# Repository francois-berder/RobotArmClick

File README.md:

## RobotArmClick

The robot arm click is a small board which uses the Mikrobus interface to control 4 servos using I2C.

This repository contains:
  - The pcb design
  - The firwmare of the PIC present on the RobotArmClick
  - Some tests to verify the firmware

For more information about the firmware and the tests, have a look at these repositories:
  - https://github.com/francois-berder/RobotArmClick-tests
  - https://github.com/francois-berder/RobotArmClick-firmware

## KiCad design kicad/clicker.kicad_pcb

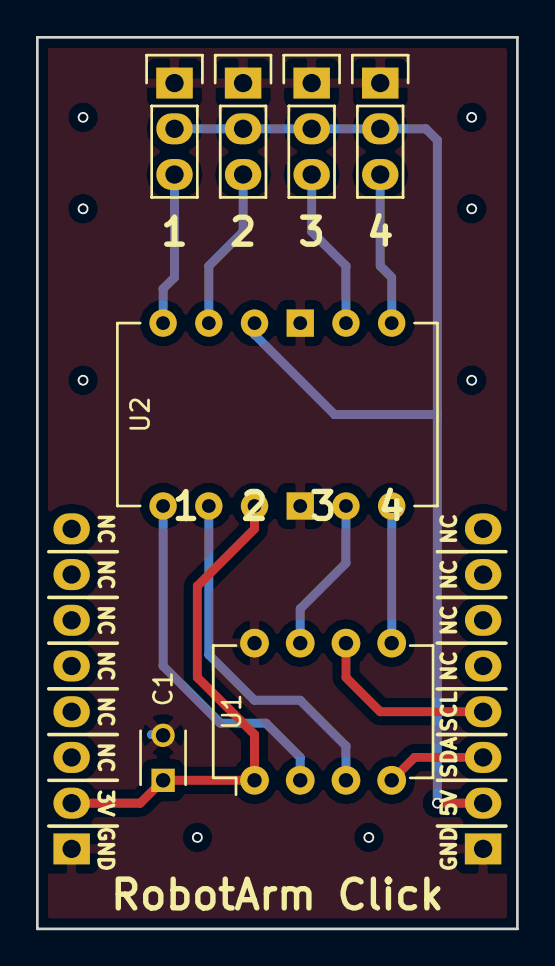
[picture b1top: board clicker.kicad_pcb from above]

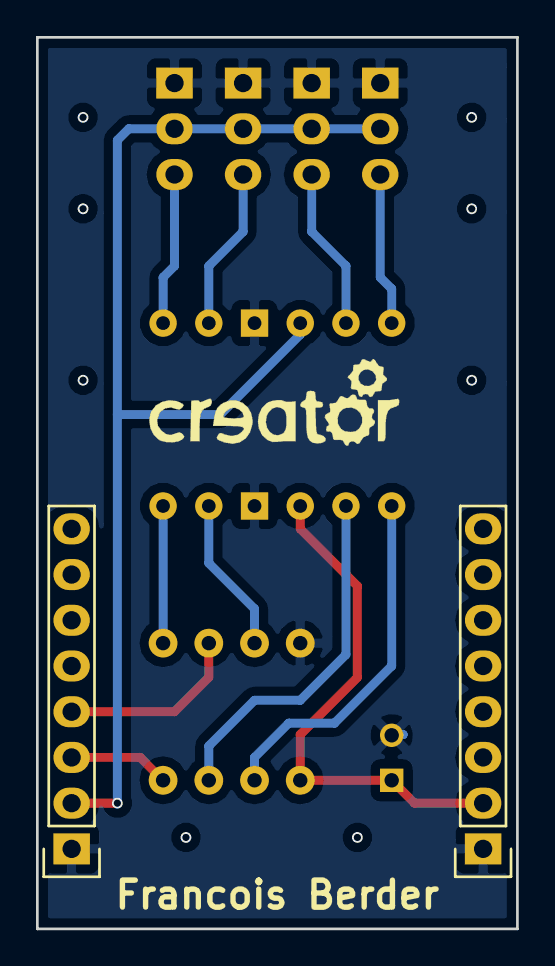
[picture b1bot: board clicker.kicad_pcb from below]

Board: 2 copper layers, 26.7 x 49.5 mm, 9 parts (2 on the bottom side), 13 nets.

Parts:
C1: C; C_Disc_D3_P2.5
U1: PIC12(L)F1552; DIP-8_W7.62mm
U2: LOGIC_LEVEL_CONVERTER
U3: MIKROBUS_CON_L; Pin_Header_Straight_1x08
U4: MIKROBUS_CON_R; Pin_Header_Straight_1x08
U5, U6, U7, U8: SERVO_CON; Pin_Header_Straight_1x03

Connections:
+3V3: C1.1, U1.1, U2.9, U3.2
+5V: U2.3, U4.2, U5.2, U6.2, U7.2, U8.2
/MIKROBUS_SCL: U1.6, U4.4
/MIKROBUS_SDA: U1.4, U4.3
/SERVO_CON_0_SIG: U1.5, U2.12
/SERVO_CON_0_SIG_5V: U2.6, U5.3
/SERVO_CON_1_SIG: U1.7, U2.11
/SERVO_CON_1_SIG_5V: U2.5, U6.3
/SERVO_CON_2_SIG: U1.3, U2.8
/SERVO_CON_2_SIG_5V: U2.2, U7.3
/SERVO_CON_3_SIG: U1.2, U2.7
/SERVO_CON_3_SIG_5V: U2.1, U8.3
GND: C1.2, U1.8, U2.4, U2.10, U3.1, U4.1, U5.1, U6.1, U7.1, U8.1

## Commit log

2017-03-04 Initial import
2017-03-04 Add readme
2017-04-02 readme: Add logo and minor change
2017-04-11 readme: Add image of board
